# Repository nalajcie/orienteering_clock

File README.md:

# Introduction
This is *work-in-progress* project to build orienteering clock, currently in prototyping phase. I will put more information here when it will be completed.

# Contents
 * `src/` - Arduino prototype source for driving multiplexed LED display and time counting. It's best to link this folder to your Arduino projects folder:
  
  ```
    in Windows:
    > mklink /D c:\Users\$USER\Documents\Arduino\orienteering_clock c:\proj\orienteering_clock\src

    in Linux:
    $ ln -s src /home/$USER/sketchbook/orienteering_clock
  ```
 
 * `schematics/` - EAGLE and PDF schematics of prototype parts. It's best to link this folder to your Eagle library:

  ```
    in Windows:
    > mklink /D c:\Users\$USER\Documents\eagle\orienteering-clock C:\proj\orienteering_clock\schematics

    in Linux:
    $ ln -s schematics /home/$USER/eagle/orienteering-clock

  ```

 * `doc/` - documentation of parts, etc.

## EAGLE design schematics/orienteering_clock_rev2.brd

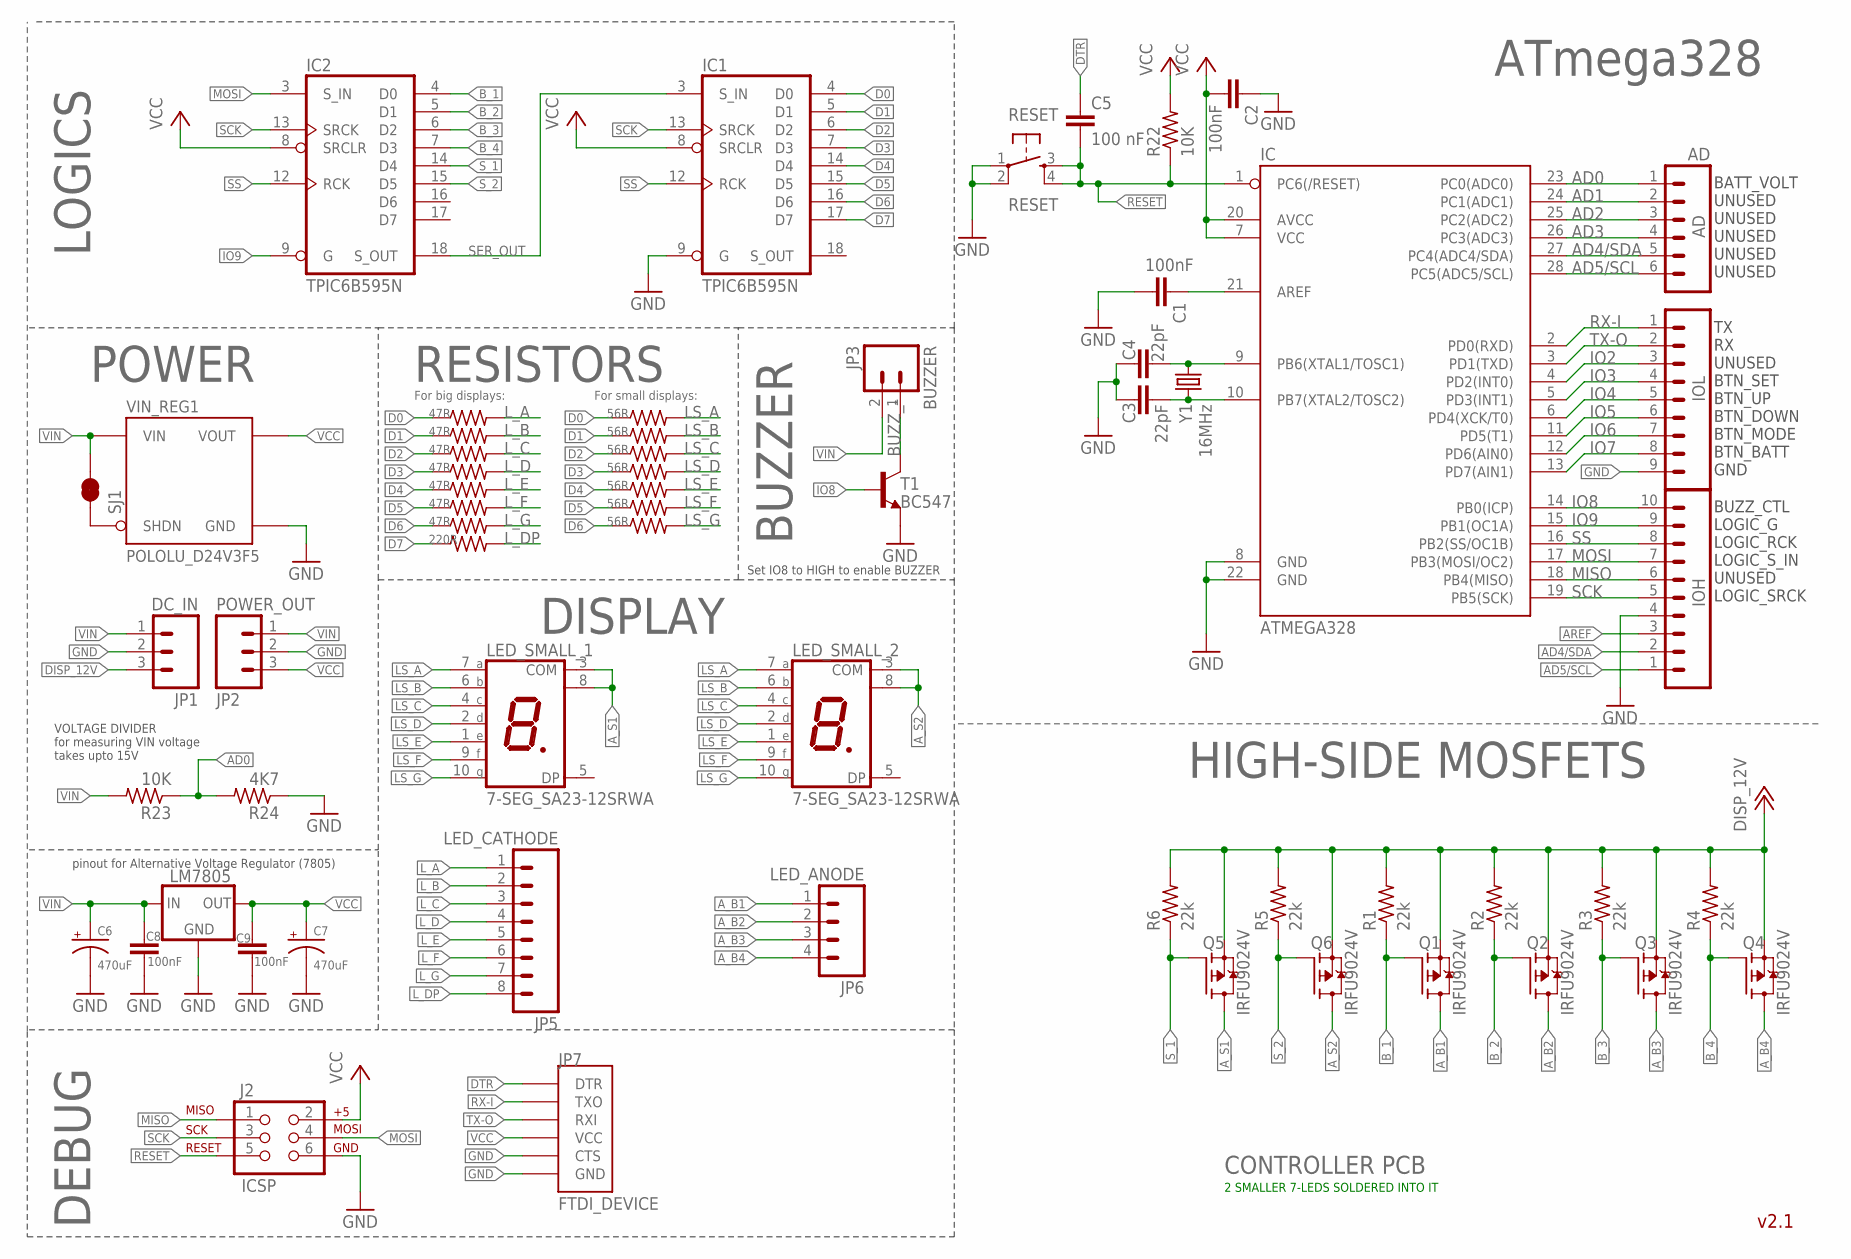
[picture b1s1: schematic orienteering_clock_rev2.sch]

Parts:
AD: AD; 1X06-SIP_LOCK
C1, C2, C8, C9: 100nF; CAP-PTH-SMALL
C3, C4: 22pF; CAP-PTH-SMALL
C5: 100 nF; CAP-PTH-SMALL
C6, C7: 470uF; CPOL-RADIAL-100UF-25V
IC: ATMEGA328; DIL28-3
IC1, IC2: TPIC6B595N; DIL20
IOH: M10LOCK; 1X10_LOCK
IOL: M09LOCK; 1X09_LOCK
J2: ICSP; 2X3_LOCK
JP1: DC_IN; MOLEX-1X3
JP2: POWER_OUT; 1X03_LOCK
JP3: BUZZER; 1X02_LOCK
JP5: LED_CATHODE; 1X08_ROUND
JP6: LED_ANODE; 1X04
JP7: FTDI_DEVICE; FTDI_DEVICE_SIDE
LED_SMALL_1, LED_SMALL_2: 7-SEG_SA23-12SRWA; SA23-12SRWA
LM7805: 78XXS
Q1, Q2, Q3, Q4, Q5, Q6: IRFU9024V; TO251AA-V
R1, R2, R3, R4, R5, R6: 22k; 0207/5V
R7, R8, R9, R10, R11, R12, R13: 47R; 0207/10
R14, R15, R16, R17, R18, R19, R20: 56R; 0207/10
R21: 220R; 0207/10
R22, R23: 10K; 0207/10
R24: 4K7; 0207/10
RESET: RESET; TACTILE-PTH
SJ1: SHDN_PULLUP; PAD-JUMPER-2-NC_BY_TRACE_YES_SILK
T1: BC547; TO92
VIN_REG1: POLOLU_D24V3F5; POLOLU_D24V3F_HC
Y1: 16MHz; HC49US

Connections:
AD0: AD.1, IC.23 (PC0(ADC0)), R23.1, R24.2
AD1: AD.2, IC.24 (PC1(ADC1))
AD2: AD.3, IC.25 (PC2(ADC2))
AD3: AD.4, IC.26 (PC3(ADC3))
AD4/SDA: AD.5, IC.27 (PC4(ADC4/SDA)), IOH.2
AD5/SCL: AD.6, IC.28 (PC5(ADC5/SCL)), IOH.1
AREF: C1.1, IC.21 (AREF), IOH.3
A_B1: JP6.1, Q1.2 (D)
A_B2: JP6.2, Q2.2 (D)
A_B3: JP6.3, Q3.2 (D)
A_B4: JP6.4, Q4.2 (D)
A_S1: LED_SMALL_1.3 (COM), LED_SMALL_1.8 (COM), Q5.2 (D)
A_S2: LED_SMALL_2.3 (COM), LED_SMALL_2.8 (COM), Q6.2 (D)
BUZZ_-: JP3.1, T1.3 (C)
B_1: IC2.4 (D0), Q1.1 (G), R1.1
B_2: IC2.5 (D1), Q2.1 (G), R2.1
B_3: IC2.6 (D2), Q3.1 (G), R3.1
B_4: IC2.7 (D3), Q4.1 (G), R4.1
D0: IC1.4 (D0), R7.1, R14.1
D1: IC1.5 (D1), R8.1, R15.1
D2: IC1.6 (D2), R9.1, R16.1
D3: IC1.7 (D3), R10.1, R17.1
D4: IC1.14 (D4), R11.1, R18.1
D5: IC1.15 (D5), R12.1, R19.1
D6: IC1.16 (D6), R13.1, R20.1
D7: IC1.17 (D7), R21.1
DISP_12V: JP1.3, Q1.3 (S), Q2.3 (S), Q3.3 (S), Q4.3 (S), Q5.3 (S), Q6.3 (S), R1.2, R2.2, R3.2, R4.2, R5.2, R6.2
DTR: C5.1, JP7.P$1 (DTR)
GND: C1.2, C2.1, C3.1, C4.1, C6.2 (-), C7.2 (-), C8.2, C9.2, IC.8 (GND), IC.22 (GND), IC1.9 (G), IC1.10 (GND), IC1.11 (GND), IC1.19 (GND), IC2.10 (GND), IC2.11 (GND), IC2.19 (GND), IOH.4, IOL.9, J2.6, JP1.2, JP2.2, JP7.P$5 (CTS), JP7.P$6 (GND), LM7805.GND, R24.1, RESET.1, RESET.2, T1.1 (E), VIN_REG1.G (GND)
IO2: IC.4 (PD2(INT0)), IOL.3
IO3: IC.5 (PD3(INT1)), IOL.4
IO4: IC.6 (PD4(XCK/T0)), IOL.5
IO5: IC.11 (PD5(T1)), IOL.6
IO6: IC.12 (PD6(AIN0)), IOL.7
IO7: IC.13 (PD7(AIN1)), IOL.8
IO8: IC.14 (PB0(ICP)), IOH.10, T1.2 (B)
IO9: IC.15 (PB1(OC1A)), IC2.9 (G), IOH.9
LS_A: LED_SMALL_1.7 (A), LED_SMALL_2.7 (A), R14.2
LS_B: LED_SMALL_1.6 (B), LED_SMALL_2.6 (B), R15.2
LS_C: LED_SMALL_1.4 (C), LED_SMALL_2.4 (C), R16.2
LS_D: LED_SMALL_1.2 (D), LED_SMALL_2.2 (D), R17.2
LS_E: LED_SMALL_1.1 (E), LED_SMALL_2.1 (E), R18.2
LS_F: LED_SMALL_1.9 (F), LED_SMALL_2.9 (F), R19.2
LS_G: LED_SMALL_1.10 (G), LED_SMALL_2.10 (G), R20.2
L_A: JP5.1, R7.2
L_B: JP5.2, R8.2
L_C: JP5.3, R9.2
L_D: JP5.4, R10.2
L_DP: JP5.8, R21.2
L_E: JP5.5, R11.2
L_F: JP5.6, R12.2
L_G: JP5.7, R13.2
MISO: IC.18 (PB4(MISO)), IOH.6, J2.1
MOSI: IC.17 (PB3(MOSI/OC2)), IC2.3 (S_IN), IOH.7, J2.4
unnamed: SJ1.2, VIN_REG1.S (SHDN)
unnamed: C4.2, IC.9 (PB6(XTAL1/TOSC1)), Y1.2
unnamed: C3.2, IC.10 (PB7(XTAL2/TOSC2)), Y1.1
RESET: C5.2, IC.1 (PC6(/RESET)), J2.5, R22.1, RESET.3, RESET.4
RX-I: IC.2 (PD0(RXD)), IOL.1, JP7.P$2 (TXO)
SCK: IC.19 (PB5(SCK)), IC1.13 (SRCK), IC2.13 (SRCK), IOH.5, J2.3
SER_OUT: IC1.3 (S_IN), IC2.18 (S_OUT)
SS: IC.16 (PB2(SS/OC1B)), IC1.12 (RCK), IC2.12 (RCK), IOH.8
S_1: IC2.14 (D4), Q5.1 (G), R6.1
S_2: IC2.15 (D5), Q6.1 (G), R5.1
TX-O: IC.3 (PD1(TXD)), IOL.2, JP7.P$3 (RXI)
VCC: C2.2, C7.1 (+), C9.1, IC.7 (VCC), IC.20 (AVCC), IC1.2 (VCC), IC1.8 (SRCLR), IC2.2 (VCC), IC2.8 (SRCLR), J2.2, JP2.3, JP7.P$4 (VCC), LM7805.OUT, R22.2, VIN_REG1.O (VOUT)
VIN: C6.1 (+), C8.1, JP1.1, JP2.1, JP3.2, LM7805.IN, R23.2, SJ1.1, VIN_REG1.I (VIN)

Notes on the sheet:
RESISTORS
LOGICS
HIGH-SIDE MOSFETS
DEBUG
For big displays:
For small displays:
ATmega328
CONTROLLER PCB
2 SMALLER 7-LEDS SOLDERED INTO IT
DISPLAY
BUZZER
POWER
VOLTAGE DIVIDER for measuring VIN voltage takes upto 15V
Set IO8 to HIGH to enable BUZZER
TX RX UNUSED BTN_SET BTN_UP BTN_DOWN BTN_MODE BTN_BATT GND
BUZZ_CTL LOGIC_G LOGIC_RCK LOGIC_S_IN UNUSED LOGIC_SRCK
BATT_VOLT UNUSED UNUSED UNUSED UNUSED UNUSED
pinout for Alternative Voltage Regulator (7805)

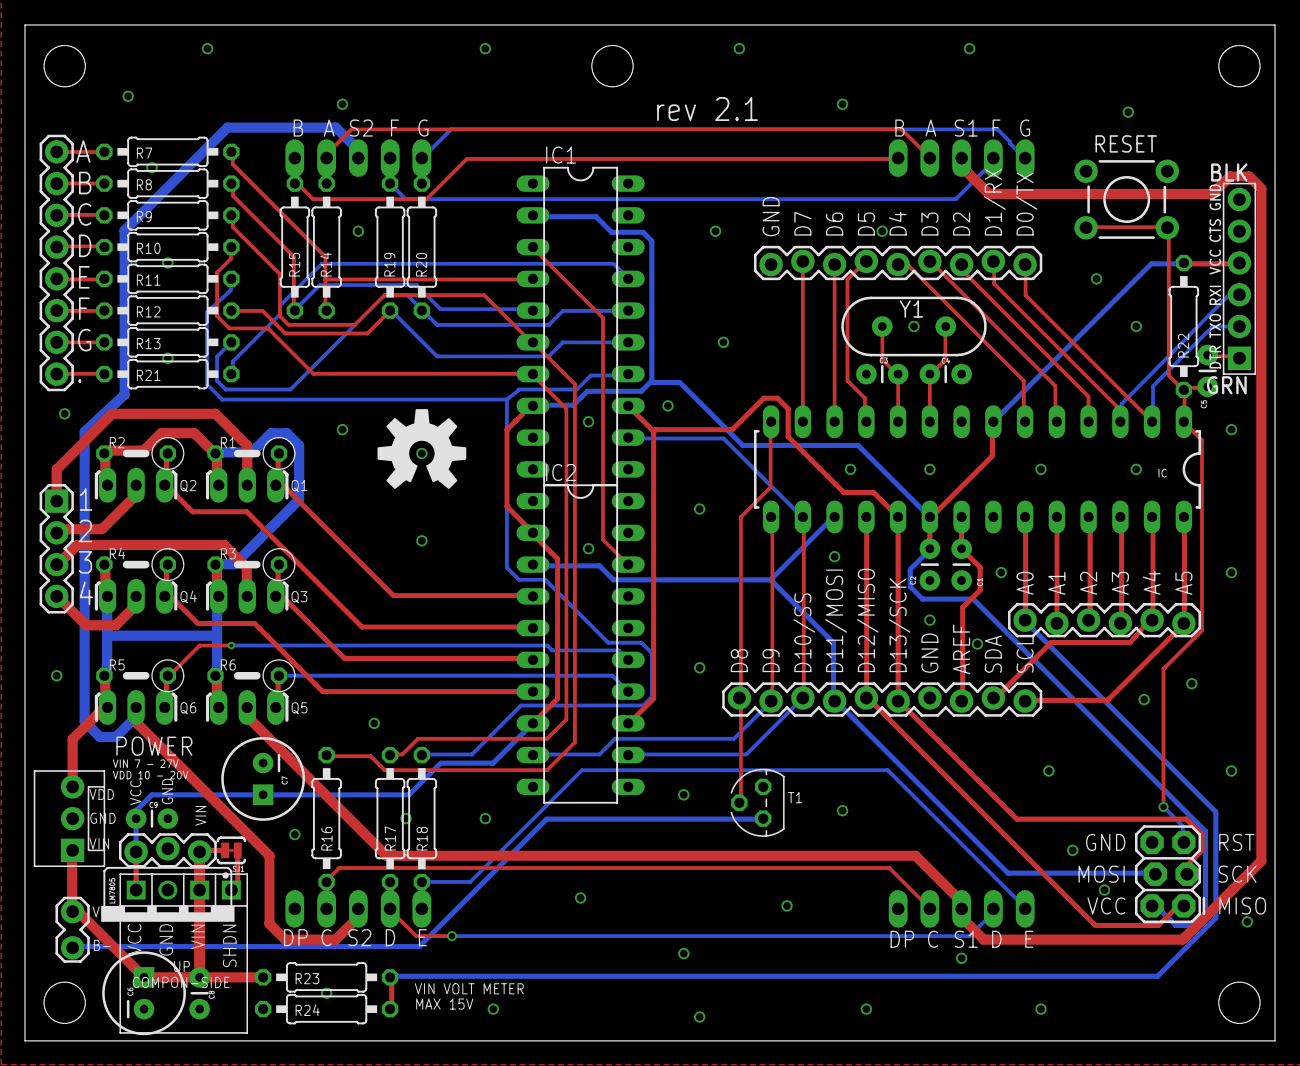
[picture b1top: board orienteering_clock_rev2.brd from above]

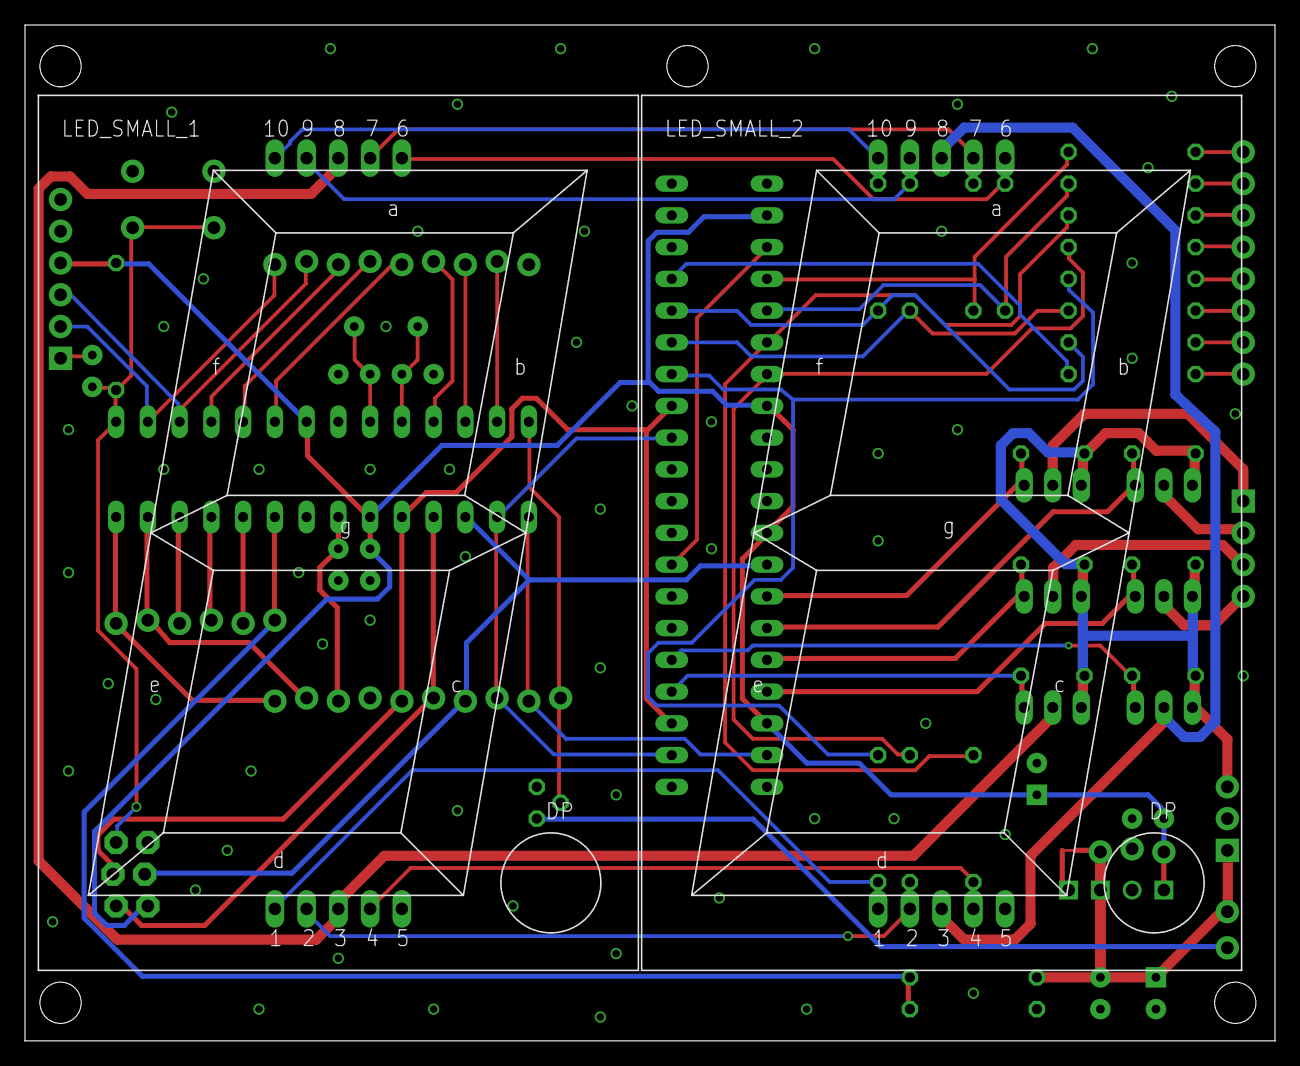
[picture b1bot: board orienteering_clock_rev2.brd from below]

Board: 2 copper layers, 100.0 x 81.3 mm, 67 parts (2 on the bottom side), 67 nets.

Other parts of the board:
E$1: OSHW-LOGO-L
E$2: DARWINIA-LOGO
JP4, JP8, JP9, JP10, JP11: STAND-OFF

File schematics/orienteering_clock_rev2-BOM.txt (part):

Partlist exported from C:/proj/orienteering_clock/schematics/orienteering_clock_rev2.sch at 2015-04-16 19:34:28

Part        Value             Device                   Package                           Description                                                          
AD          AD                M06SIP_LOCK              1X06-SIP_LOCK                     Header 6                                                             
C1          100nF             CAPPTH                   CAP-PTH-SMALL                     Capacitor                                                            
C2          100nF             CAPPTH                   CAP-PTH-SMALL                     Capacitor                                                            
C3          22pF              CAPPTH                   CAP-PTH-SMALL                     Capacitor                                                            
C4          22pF              CAPPTH                   CAP-PTH-SMALL                     Capacitor                                                            
C5          0.1uF             CAPPTH                   CAP-PTH-SMALL                     Capacitor                                                            
C6          470uF             CAP_POLPTH1              CPOL-RADIAL-100UF-25V             Capacitor Polarized                                                  
C7          470uF             CAP_POLPTH1              CPOL-RADIAL-100UF-25V             Capacitor Polarized                                                  
C8          100nF             CAPPTH                   CAP-PTH-SMALL                     Capacitor                                                            
C9          100nF             CAPPTH                   CAP-PTH-SMALL                     Capacitor                                                            
IC          ATMEGA328         ATMEGA328P_PDIP          DIL28-3                           uC used in the Arduino                                               
IC1         TPIC6B595N        TPIC6B595N               DIL20                             8-bit SHIFT REGISTER, output latch                                   
IC2         TPIC6B595N        TPIC6B595N               DIL20                             8-bit SHIFT REGISTER, output latch                                   
IOH         M10LOCK           M10LOCK                  1X10_LOCK                         Header 10                                                            
IOL         M09LOCK           M09LOCK                  1X09_LOCK                         Header 9                                                             
J2          ICSP              AVR_SPI_PRG_62X3_LOCK    2X3_LOCK                          AVR ISP 6 Pin                                                        
JP1         DC_IN             M03POLAR                 MOLEX-1X3                         Header 3                                                             
JP2         POWER_OUT         M03LOCK                  1X03_LOCK                         Header 3                                                             
JP3         BUZZER            M02LOCK                  1X02_LOCK                         Standard 2-pin 0.1" header. Use with                                 
JP5         LED_CATHODE       M08                      1X08_ROUND                        Header 8                                                             
JP6         LED_ANODE         M04PTH                   1X04                              Header 4                                                             
JP7         FTDI_DEVICE       FTDI_DEVICE              FTDI_DEVICE_SIDE                  Connector which mates to FTDI basic or FTDI cable.                   
LED_SMALL_1 7-SEG_SA23-12SRWA 7-SEG_SA23-12SRWA        SA23-12SRWA                       Kingbright 14.2mm (0.56 INCH) SINGLE DIGIT NUMERIC DUISPLAY          
LED_SMALL_2 7-SEG_SA23-12SRWA 7-SEG_SA23-12SRWA        SA23-12SRWA                       Kingbright 14.2mm (0.56 INCH) SINGLE DIGIT NUMERIC DUISPLAY          
LM7805                        78XXS                    78XXS                             VOLTAGE REGULATOR - NO DRILL                                         
Q1          IRFU9024V         IRFU9024V                TO251AA-V                         P-CHANNEL MOSFET                                                     
Q2          IRFU9024V         IRFU9024V                TO251AA-V                         P-CHANNEL MOSFET                                                     
Q3          IRFU9024V         IRFU9024V                TO251AA-V                         P-CHANNEL MOSFET                                                     
Q4          IRFU9024V         IRFU9024V                TO251AA-V                         P-CHANNEL MOSFET                                                     
Q5          IRFU9024V         IRFU9024V                TO251AA-V                         P-CHANNEL MOSFET                                                     
Q6          IRFU9024V         IRFU9024V                TO251AA-V                         P-CHANNEL MOSFET                                                     
R1          22k               R-US_0207/5V             0207/5V                           RESISTOR, American symbol                                            
R2          22k               R-US_0207/5V             0207/5V                           RESISTOR, American symbol                                            
R3          22k               R-US_0207/5V             0207/5V                           RESISTOR, American symbol                                            
R4          22k               R-US_0207/5V             0207/5V                           RESISTOR, American symbol                                            
R5          22k               R-US_0207/5V             0207/5V                           RESISTOR, American symbol                                            
R6          22k               R-US_0207/5V             0207/5V                           RESISTOR, American symbol                                            
R7          22R               R-US_0207/10             0207/10                           RESISTOR, American symbol                                            
R8          22R               R-US_0207/10             0207/10                           RESISTOR, American symbol                                            
R9          22R               R-US_0207/10             0207/10                           RESISTOR, American symbol                                            
R10         22R               R-US_0207/10             0207/10                           RESISTOR, American symbol                                            
R11         22R               R-US_0207/10             0207/10                           RESISTOR, American symbol                                            
R12         22R               R-US_0207/10             0207/10                           RESISTOR, American symbol                                            
R13         22R               R-US_0207/10             0207/10                           RESISTOR, American symbol                                            
R14         56R               R-US_0207/10             0207/10                           RESISTOR, American symbol                                            
R15         56R               R-US_0207/10             0207/10                           RESISTOR, American symbol                                            
R16         56R               R-US_0207/10             0207/10                           RESISTOR, American symbol                                            
R17         56R               R-US_0207/10             0207/10                           RESISTOR, American symbol                                            
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
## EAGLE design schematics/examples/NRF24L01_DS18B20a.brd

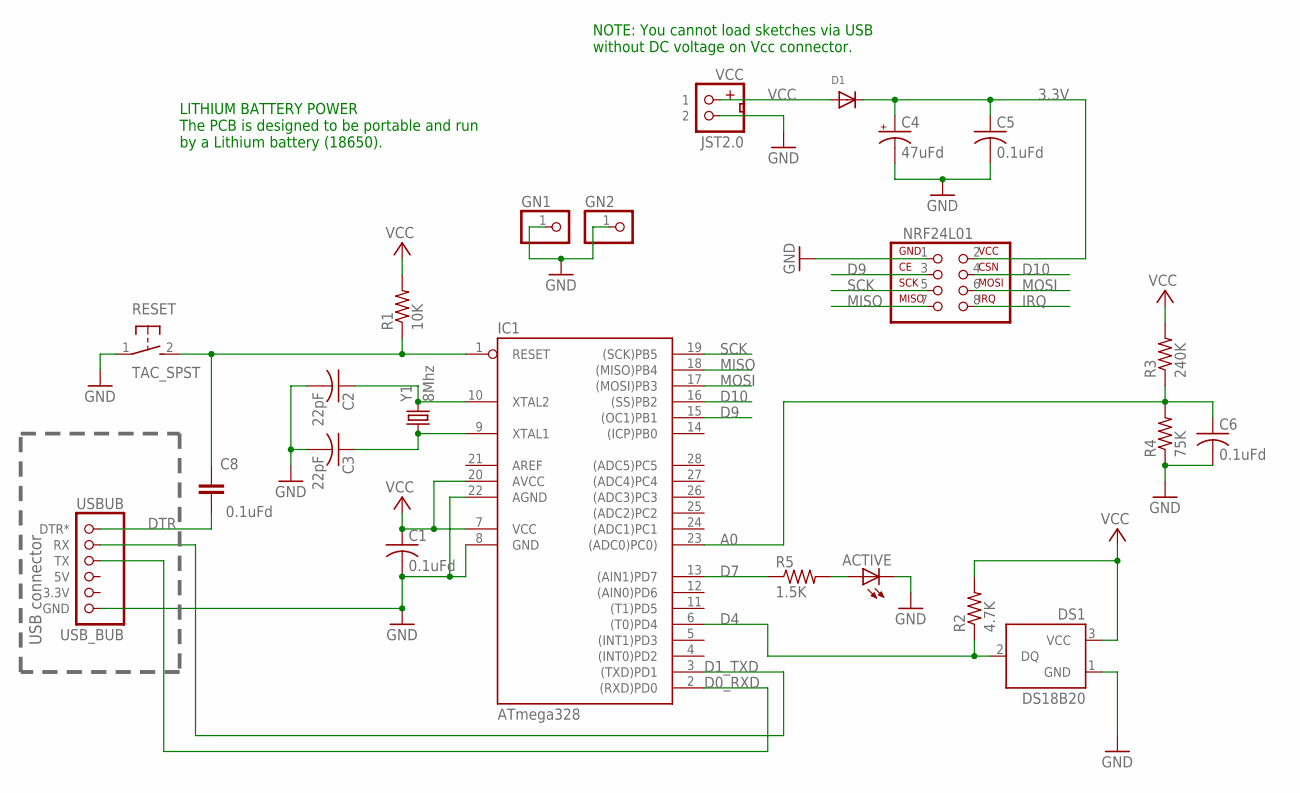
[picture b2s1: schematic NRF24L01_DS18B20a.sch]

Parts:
ACTIVE: LED3MM
C1, C5, C6: 0.1uFd; C025-025X050
C2, C3: 22pF; C025-025X050
C4: 47uFd; E2,5-6
C8: 0.1uFd; C050-025X075
D1: DIODEDO-1N4148; DO-1N4148
DS1: DS18B20
GN1, GN2: PINHD-1X1; 1X01
IC1: ATmega328; DIL28-3
NRF24L01: NRF24L01+
R1: 10K; 0207/2V
R2: 4.7K; 0207/2V
R3: 240K; 0207/10
R4: 75K; 0207/2V
R5: 1.5K; 0207/2V
RESET: TAC_SPST; TACTILE-SPST
USBUB: USB_BUB
VCC: JST2.0
Y1: 8Mhz; TC38H

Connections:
3.3V: C4.+, C5.1, D1.C, NRF24L01.2
A0: C6.1, IC1.23 ((ADC0)PC0)), R3.1, R4.2
D0_RXD: IC1.2 ((RXD)PD0), USBUB.TX
D1_TXD: IC1.3 ((TXD)PD1), USBUB.RX
D4: DS1.2 (DQ), IC1.6 ((T0)PD4), R2.1
D7: IC1.13 ((AIN1)PD7), R5.1
D9: IC1.15 ((OC1)PB1), NRF24L01.3
D10: IC1.16 ((SS)PB2), NRF24L01.4
DTR: C8.1, USBUB.DTR*
GND: ACTIVE.K (C), C1.2, C2.2, C3.2, C4.-, C5.2, C6.2, DS1.1 (GND), GN1.1, GN2.1, IC1.8 (GND), IC1.22 (AGND), NRF24L01.1, R4.1, RESET.1, USBUB.GND, VCC.2
IRQ: NRF24L01.8
MISO: IC1.18 ((MISO)PB4), NRF24L01.7
MOSI: IC1.17 ((MOSI)PB3), NRF24L01.6
unnamed: ACTIVE.A, R5.2
unnamed: C3.1, IC1.9 (XTAL1), Y1.1
unnamed: C2.1, IC1.10 (XTAL2), Y1.2
RESET: C8.2, IC1.1 (RESET), R1.1, RESET.2
SCK: IC1.19 ((SCK)PB5), NRF24L01.5
VCC: C1.1, D1.A, DS1.3 (VCC), IC1.7 (VCC), IC1.20 (AVCC), R1.2, R2.2, R3.2, VCC.1

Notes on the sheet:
USB connector
LITHIUM BATTERY POWER The PCB is designed to be portable and run by a Lithium battery (18650).
NOTE: You cannot load sketches via USB without DC voltage on Vcc connector.

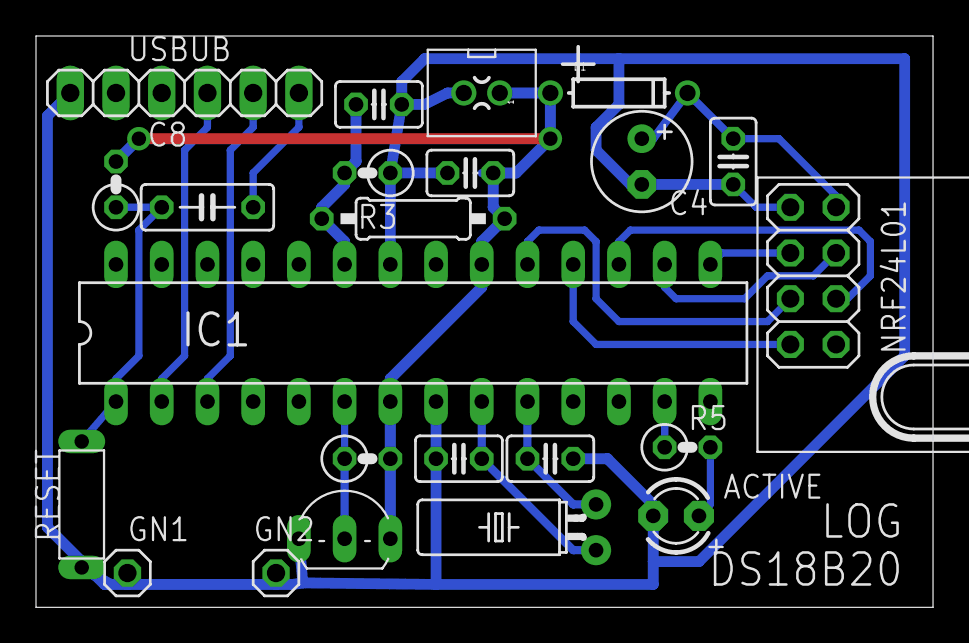
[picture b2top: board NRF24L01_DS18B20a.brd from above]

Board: 2 copper layers, 49.8 x 31.7 mm, 23 parts (0 on the bottom side), 18 nets.

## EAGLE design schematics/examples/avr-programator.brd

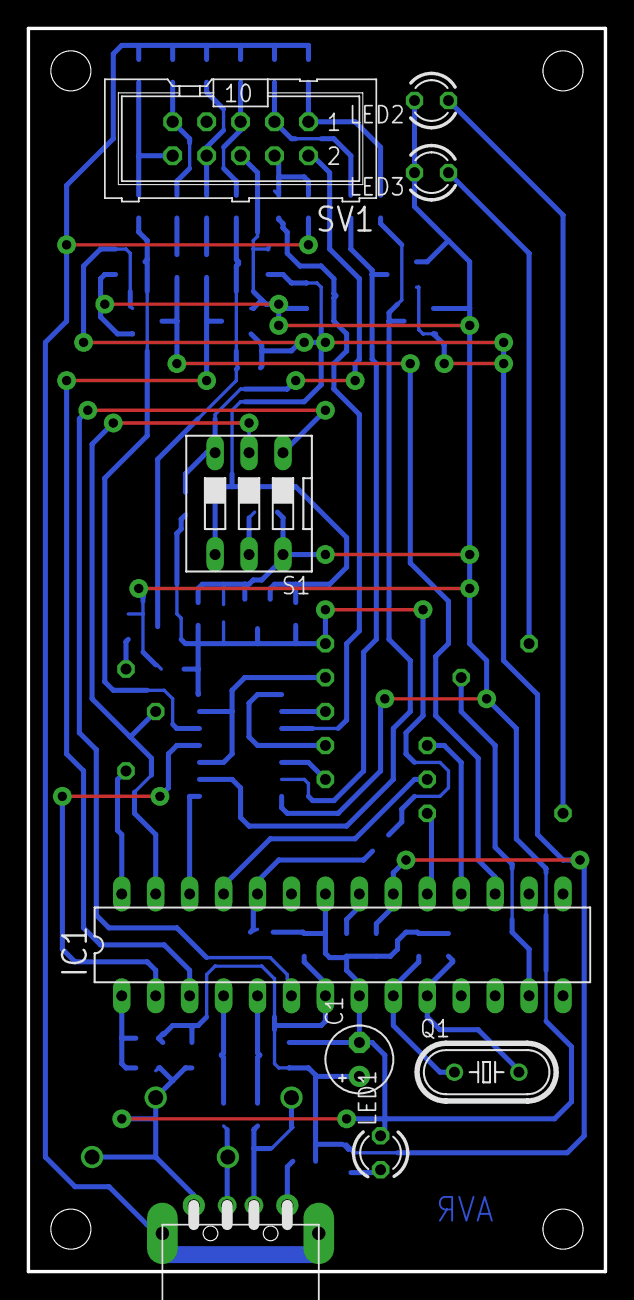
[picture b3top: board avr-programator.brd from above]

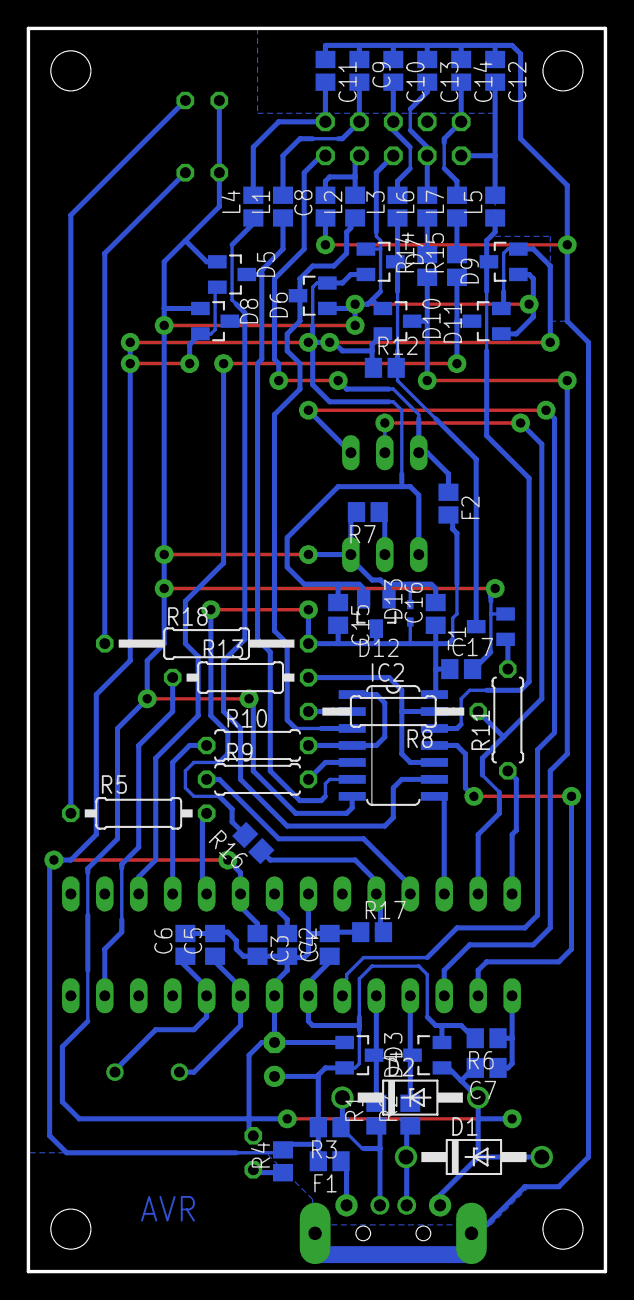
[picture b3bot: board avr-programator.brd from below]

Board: 2 copper layers, 43.2 x 93.0 mm, 67 parts (58 on the bottom side), 49 nets.

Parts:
C1: 4u7F; E2,5-5
C2, C3, C4, C7, C15, C16, C17: 100nF; C0805
C5, C6: 22pF; C0805
C8, C9, C10, C11, C12, C13, C14: 10pF; C0805
D1, D2: Z3V6; DO41Z10
D3, D4, D5, D6, D7, D8, D9, D10, D11, D12: BAV199; SOT23
D13: Z5V1; SOD523
F1, F2: 0.5A; 0805
IC1: MEGA8-P; DIL28-3
IC2: 74HC126D; SO14
L1, L2, L3, L4, L5, L6, L7: bead; 0805
LED1, LED3: grn; LED3MM
LED2: red; LED3MM
Q1: 12MHZ; HC49/S
R1, R2: 68R; R0805
R3: 2k2; R0805
R4: 1k8; R0805
R5: 1k8; 0207/10
R6: 10k; R0805
R7, R12, R14, R15: 1k; R0805
R8: 10k; 0207/12
R9, R10, R11: 10k; 0207/7
R13: 10k; 0207/10
R16: 33k; R0805
R17: 22k; R0805
R18: 1k8; 0207/15
S1: settings; DS-03
SV1: isp; ML10
T1: BC847; SOT23
X1: usb; MC32603P

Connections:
CLK_S: C14.2, L7.2, SV1.9
D+: D1.C, R2.1, X1.3
D-: D2.C, R1.1, R3.1, X1.2
DRIVER_EN: IC1.18, R10.1
GND: C1.-, C2.2, C3.2, C4.2, C5.2, C6.2, C7.2, C16.2, C17.2, D1.A, D2.A, D3.1, D4.1, D5.1, D6.1, D7.1, D8.1, D9.1, D10.1, D11.1, D12.1, D13.A, IC1.8, IC1.22, IC2.7, LED1.K, LED2.K, LED3.K, R7.2, R17.1, S1.6, SV1.6, T1.2, X1.4
ISP_CLK: D11.3, IC1.17, R15.1
ISP_RESET: IC1.28, R11.1
ISP_SUP_PRESENT: IC1.24, R16.1, R17.2
ISP_TMISO: IC1.26, IC2.8
ISP_TMOSI: IC1.27, R8.1, S1.2
ISP_TSCK: IC1.25, R9.1
unnamed: F1.1, X1.1
unnamed: C4.1, IC1.21
unnamed: C6.1, IC1.10, Q1.2
unnamed: LED1.A, R4.1
unnamed: C5.1, IC1.9, Q1.1
unnamed: LED2.A, R5.1
unnamed: C7.1, IC1.1, R6.1
unnamed: IC1.19, R5.2
unnamed: R7.1, S1.5
unnamed: IC2.2, R8.2
unnamed: IC2.5, R9.2
unnamed: D6.3, IC2.3, L2.1
unnamed: IC2.1, IC2.4, R10.2
unnamed: D5.3, IC2.6, L1.1
unnamed: R11.2, T1.1
unnamed: D7.3, L3.1, R12.2, T1.3
unnamed: D8.3, IC2.9, L4.1
unnamed: D9.3, IC2.12, L5.1
unnamed: IC2.10, IC2.13, R13.2
unnamed: L6.1, R14.2
unnamed: L7.1, R15.2
unnamed: C15.2, C16.1, C17.1, D12.3, D13.C, F2.2, IC2.14, R16.2, R18.2
unnamed: LED3.A, R18.1
REC_EN: IC1.13, R13.1
RESET_S: C10.2, L3.2, SV1.5
RXD: IC1.2, IC2.11
RXD_S: C13.2, L6.2, SV1.8
SHIELD: C8.1, C9.1, C10.1, C11.1, C12.1, C13.1, C14.1, X1.S1, X1.S2
SLOW_SCK: IC1.6, S1.1
TMISO_S: C11.2, L4.2, SV1.1
TMOSI_S: C8.2, L2.2, SV1.4
TSCK_S: C9.2, L1.2, SV1.3
TXD: D10.3, IC1.3, R14.1
TXD_S: C12.2, L5.2, SV1.10
USBM: D3.3, IC1.5, R1.2
USBP: D4.3, IC1.4, R2.2
VCC: C1.+, C2.1, C3.1, C15.1, D3.2, D4.2, D5.2, D6.2, D7.2, D8.2, D9.2, D10.2, D11.2, D12.2, F1.2, IC1.7, IC1.20, R3.2, R4.2, R6.2, R12.1, S1.4
VTG: F2.1, S1.3, SV1.2

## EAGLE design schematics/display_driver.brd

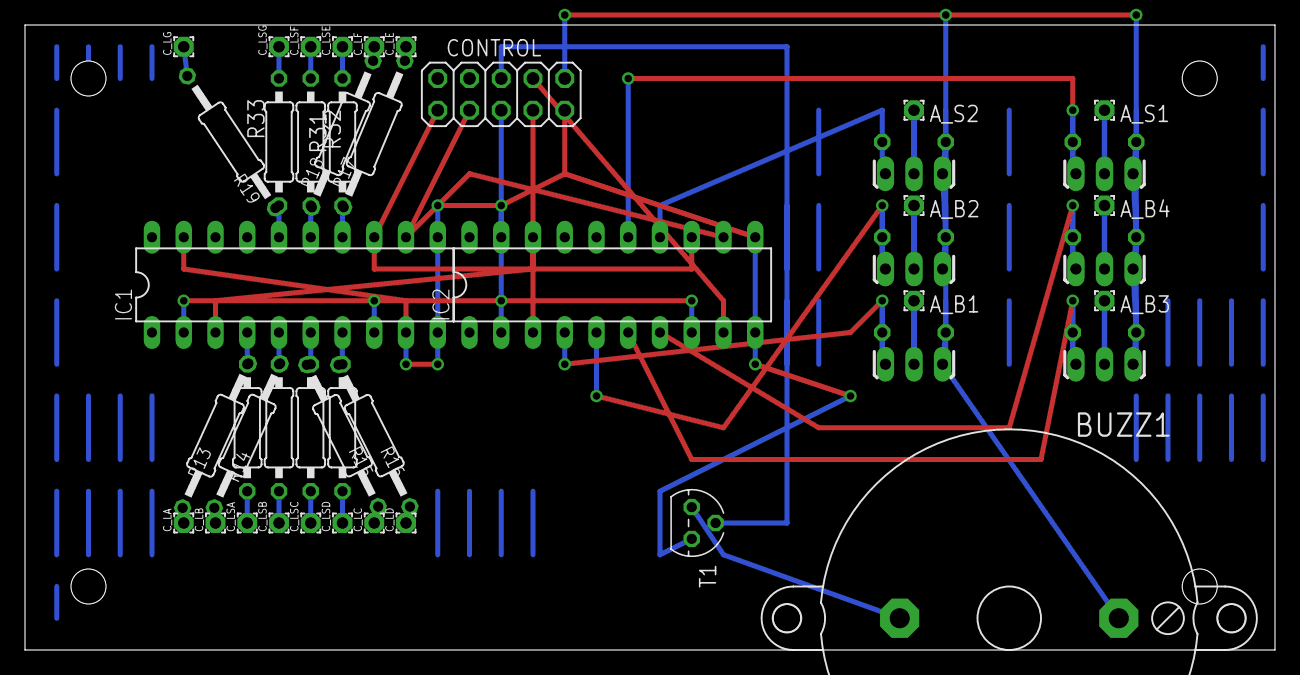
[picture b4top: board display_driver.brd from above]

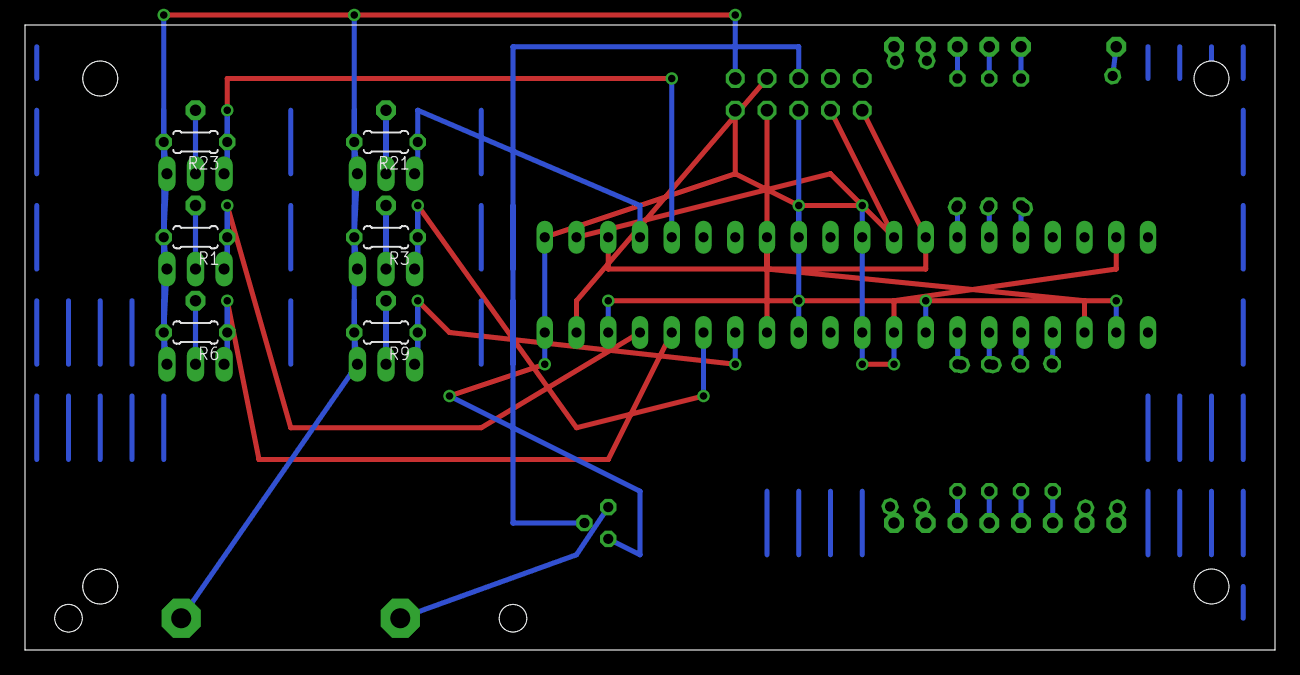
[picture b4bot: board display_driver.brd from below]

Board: 2 copper layers, 100.0 x 50.0 mm, 51 parts (6 on the bottom side), 43 nets.

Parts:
A_B1, A_B2, A_B3, A_B4: 1,6/0,9
A_S1, A_S2: 1,6/0,9
BUZZ1: F/BC40
CONTROL: JP_1; 2X05
C_LA: 1,6/0,9
C_LB: 1,6/0,9
C_LC: 1,6/0,9
C_LD: 1,6/0,9
C_LE: 1,6/0,9
C_LF: 1,6/0,9
C_LG: 1,6/0,9
C_LSA: 1,6/0,9
C_LSB: 1,6/0,9
C_LSC: 1,6/0,9
C_LSD: 1,6/0,9
C_LSE: 1,6/0,9
C_LSF: 1,6/0,9
C_LSG: 1,6/0,9
IC1, IC2: TPIC6B595N; DIL20
Q1, Q2, Q3, Q4, Q5, Q6: IRFU9024V; TO251AA-V
R1, R3, R6, R9, R21, R23: 22k; 0204/5
R13, R14, R15, R16, R17, R18, R19: 22R; 0207/12
R27, R28, R29, R30, R31, R32, R33: 56R; 0207/10
T1: BC547; TO92

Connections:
+12V: BUZZ1.+, CONTROL.10, Q1.3, Q2.3, Q3.3, Q4.3, Q5.3, Q6.3, R1.2, R3.2, R6.2, R9.2, R21.2, R23.2
BUZZ_CTL: CONTROL.6, T1.2
B_1: IC2.4, Q1.1, R9.1
B_2: IC2.5, Q2.1, R3.1
B_3: IC2.6, Q3.1, R6.1
B_4: IC2.7, Q4.1, R1.1
D0: IC1.4, R13.1, R27.1
D1: IC1.5, R14.1, R28.1
D2: IC1.6, R15.1, R29.1
D3: IC1.7, R16.1, R30.1
D4: IC1.14, R17.1, R31.1
D5: IC1.15, R18.1, R32.1
D6: IC1.16, R19.1, R33.1
G: CONTROL.8, IC2.9
GND: CONTROL.9, IC1.9, IC1.10, IC1.11, IC1.19, IC2.10, IC2.11, IC2.19, T1.1
LS_A: C_LSA.1, R27.2
LS_B: C_LSB.1, R28.2
LS_C: C_LSC.1, R29.2
LS_D: C_LSD.1, R30.2
LS_E: C_LSE.1, R31.2
LS_F: C_LSF.1, R32.2
LS_G: C_LSG.1, R33.2
L_A: C_LA.1, R13.2
L_B: C_LB.1, R14.2
L_C: C_LC.1, R15.2
L_D: C_LD.1, R16.2
L_E: C_LE.1, R17.2
L_F: C_LF.1, R18.2
L_G: C_LG.1, R19.2
unnamed: A_B1.1, Q1.2
unnamed: BUZZ1.-, T1.3
unnamed: A_B2.1, Q2.2
unnamed: A_B3.1, Q3.2
unnamed: A_B4.1, Q4.2
unnamed: IC1.3, IC2.18
unnamed: A_S2.1, Q6.2
unnamed: A_S1.1, Q5.2
RCK: CONTROL.3, IC1.12, IC2.12
SER_IN: CONTROL.7, IC2.3
SRCK: CONTROL.1, IC1.13, IC2.13
S_1: IC2.15, Q5.1, R23.1
S_2: IC2.14, Q6.1, R21.1
VCC: CONTROL.5, IC1.2, IC1.8, IC2.2, IC2.8

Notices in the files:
parts and their libraries:
SparkFun-Aesthetics: Licensing: CC v3.0 Share-Alike You are welcome to use this library for commercial purposes.
SparkFun-Aesthetics: Released under the Creative Commons Attribution Share-Alike 3.0 License
SparkFun-Aesthetics: http://creativecommons.org/licenses/by-sa/3.0
